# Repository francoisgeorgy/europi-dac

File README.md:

# A 4 channels DAC for the EuroPi

This is a custom PCB that add a four channels DAC to the [EuroPi](https://allensynthesis.co.uk/modules/europi.html).

The DAC is a [MCP4728](https://www.microchip.com/en-us/product/mcp4728) : 

* 12-Bit Resolution
* 4 Buffered Voltage Outputs
* Single-Supply Operation: 2.7V to 5.5V
* On-Board Non-Volatile Memory (EEPROM)
* Normal or Power-Down Mode
* Internal or External Voltage Reference Selection
* Rail-to-Rail Output
* Low Power Consumption
* ±0.2 LSB DNL (typical)
* Address bits: User Programmable toEEPROM
* Standard (100 kbps), Fast (400 kbps) and High Speed (3.4 Mbps) Modes

The voltage reference is a [LM4040](https://www.analog.com/en/products/lm4040.html), 3.0V. 

The DAC outputs are connected to the EuroPi 3, 4, 5 and 6 outputs as follows : 

| EuroPi output | DAC channel |
|--------------:|------------:|
|             1 |             |
|             2 |             |
|             3 |           D |
|             4 |           B |
|             5 |           C |
|             6 |           A |

This specific order of the channels was chosen to facilitate the PCB routing. 

The EuroPi outputs 1 and 2 do not change and are still driven with a PWM output from the Pico.

#### Power supply : 

This custom PCB swaps the 10-pin Eurorack power connector for a 16-pin one and removes the onboard power regulator, 
opting to use the 5V directly from the Eurorack power supply instead.

## Schematic

Here is the schematic of this PCB : [dac-board-v2.1.pdf](hardware%2Fdac-board-v2.1%2Fplot%2Fdac-board-v2.1.pdf)

## Why build this custom PCB?

This PCB project was mainly a fun excuse to experiment and learn:

- [KiCad](https://www.kicad.org/) practice: a good opportunity to get better at PCB design.
- SMD assembly with [JLCPCB](https://jlcpcb.com/): tried out having the board made and assembled by an external provider.
- Eurorack power filtering: played around with filtering power right on the PCB.
- DAC vs PWM outputs: wanted to see if DAC outputs really outperform PWM for basic CV voltages.
- Just for fun: because DIY projects are always more fun!

## License

This custom PCB is licensed under the same terms and conditions as the original EuroPi. 

This module, and any documentation included in this repository, is entirely "free" software and hardware, 
under different licenses depending on the software, hardware, and documentation itself.

* Software: [Apache 2.0](software/LICENSE)
* Hardware: [CERN OHL-S v2](hardware/LICENSE)
* Documentation: [CC0 1.0](LICENSE)

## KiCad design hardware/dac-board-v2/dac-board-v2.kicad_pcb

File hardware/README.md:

## PCB versions

### [dac-board](dac-board) 

Do not use this version. The J2 and J3 connectors (headers that link the front panel) are incorrectly oriented.

### [dac-board-v2](dac-board-v2) 

This version is OK and has been successfully used with a regular EuroPi front-panel. 

### [dac-board-v2.1](dac-board-v2.1) 

This minor release fixes the connectors placement in KiCad. This version has not been tested yet.

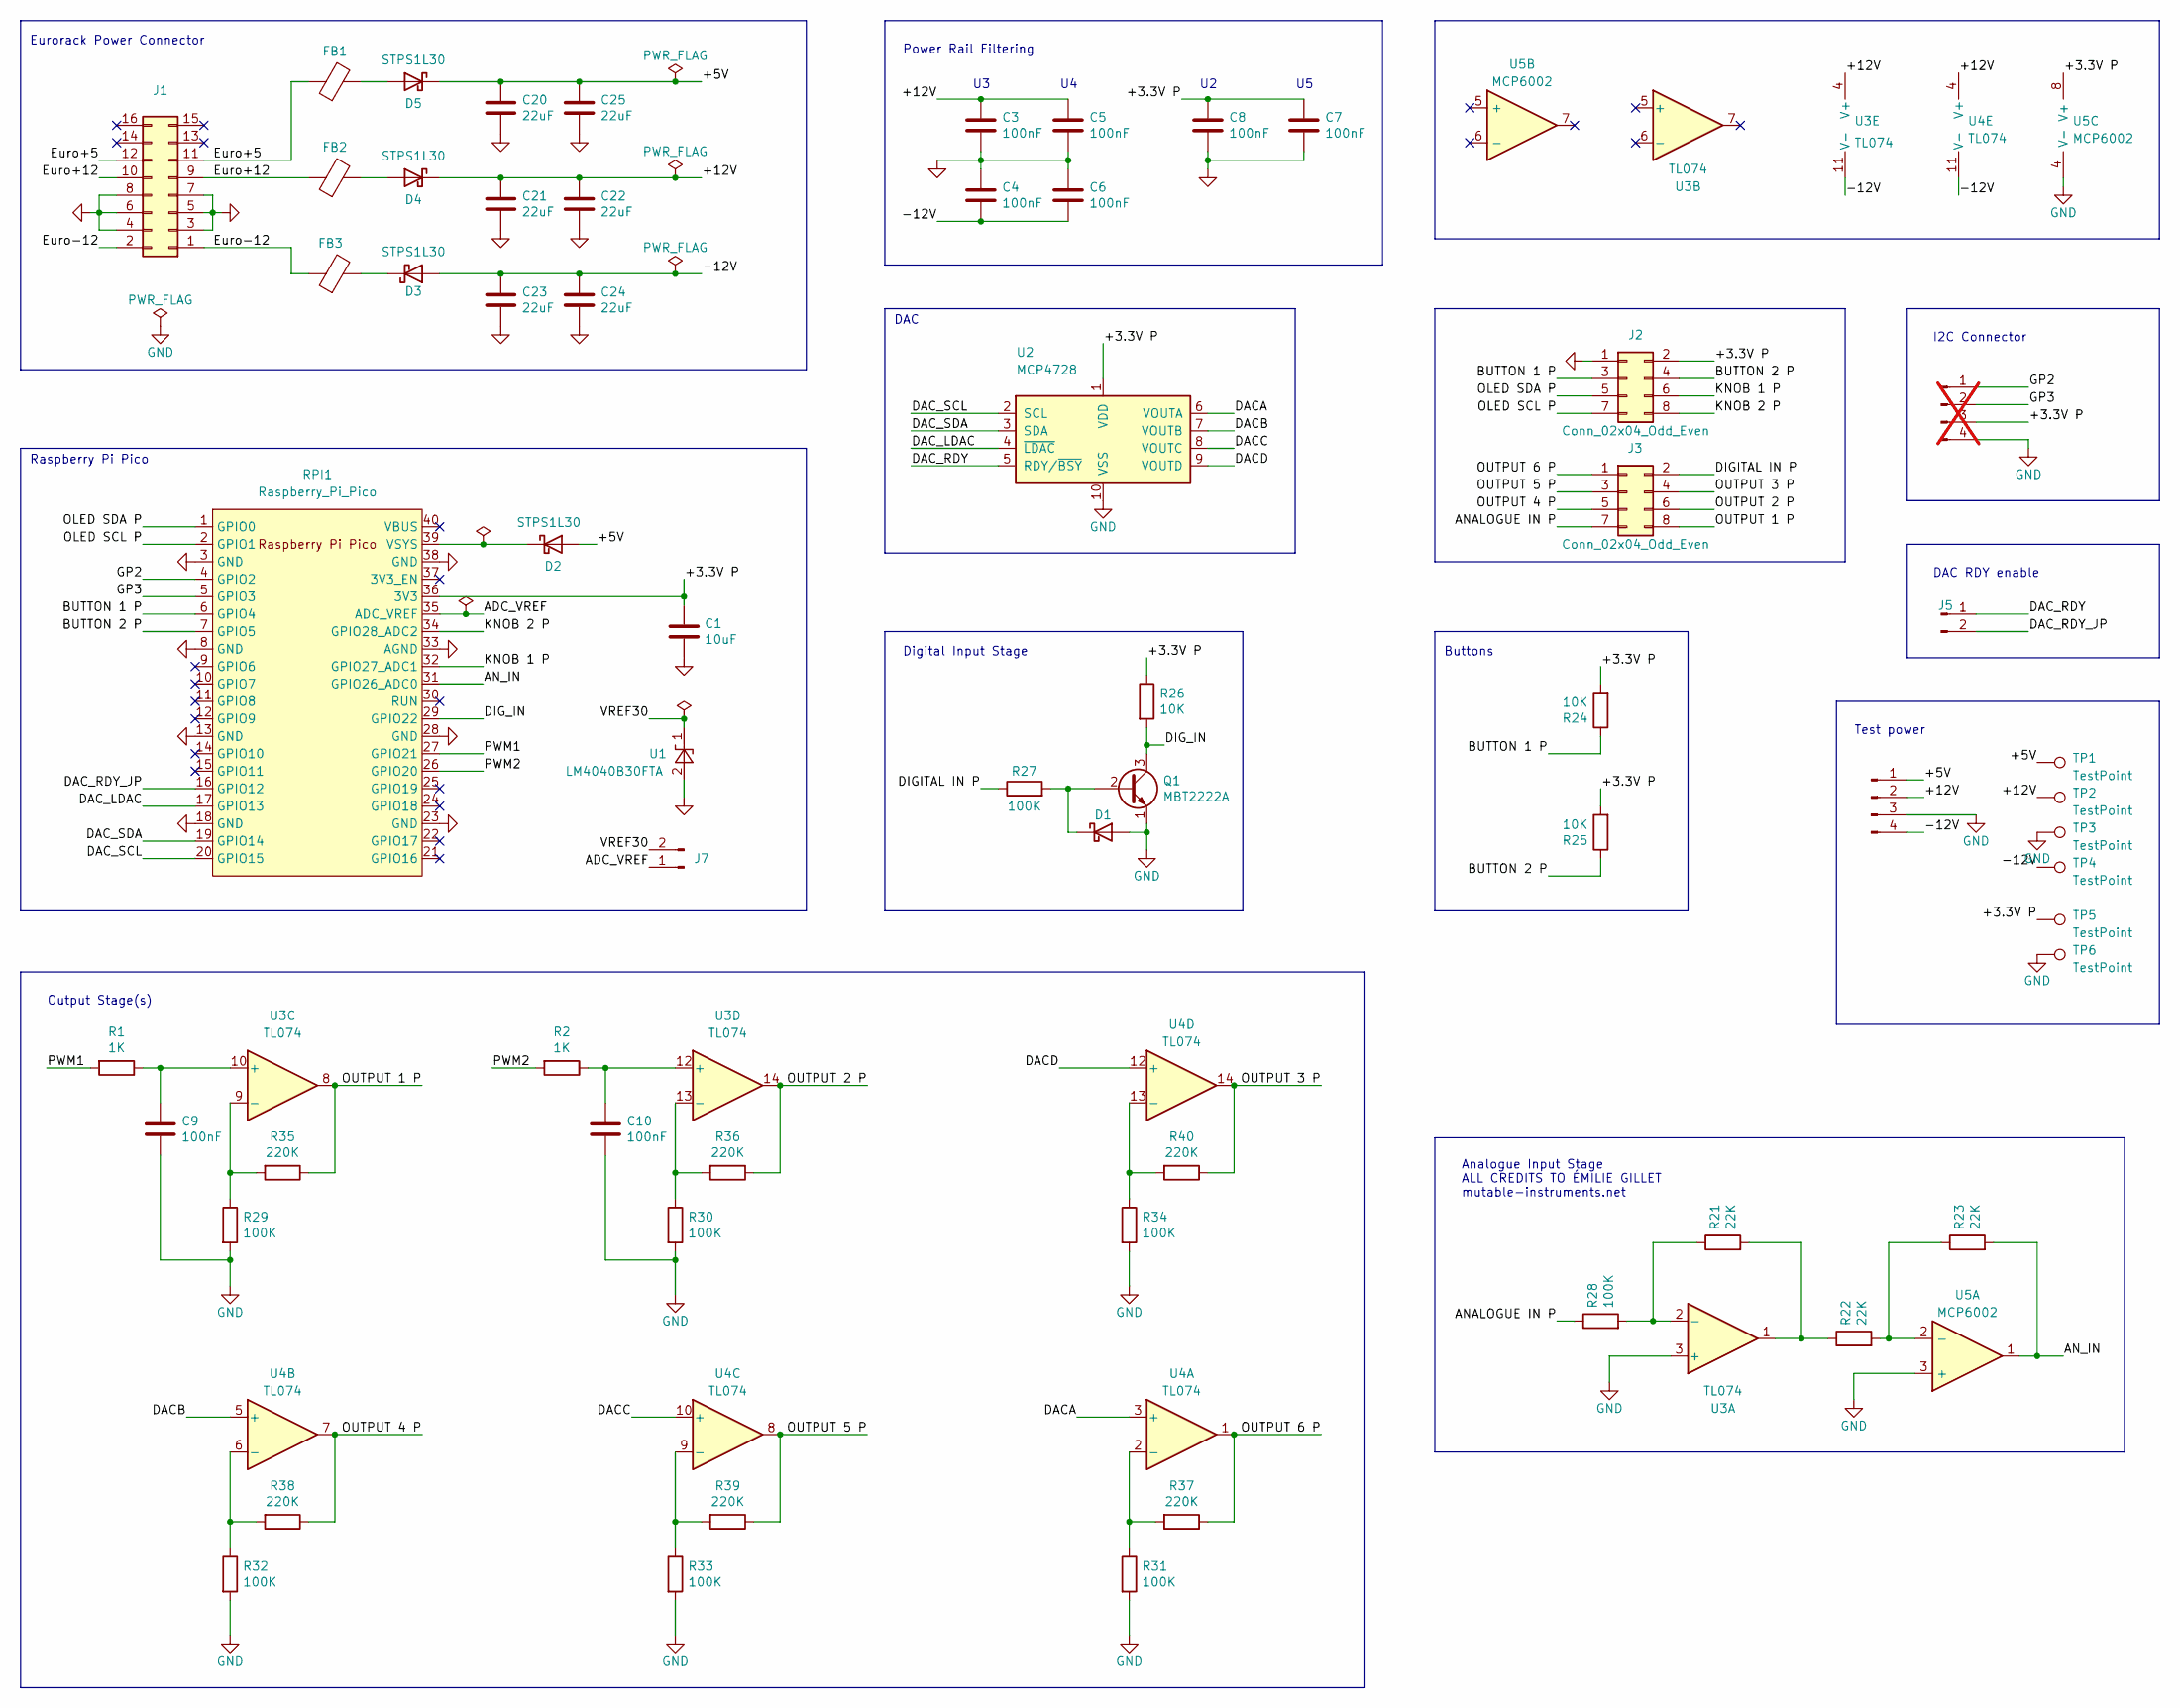
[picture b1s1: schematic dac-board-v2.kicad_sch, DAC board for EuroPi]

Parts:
C1: 10uF; C_0805_2012Metric; JLCPCB Part # C15850
C3, C4, C5, C6, C7, C8, C9, C10: 100nF; C_0402_1005Metric
C20, C21, C22, C23, C24, C25: 22uF; C_1206_3216Metric; JLCPCB Part # C12891
D1: 1N5817WS; D_SOD-323; JLCPCB Part # C727114
D2, D3, D4, D5: STPS1L30; D_SMA; JLCPCB Part # C157388
FB1, FB2, FB3: FerriteBead; L_0805_2012Metric; JLCPCB Part # C216152
J1: Conn_02x08_Odd_Even; IDC-Header_2x08_P2.54mm_Vertical
J2, J3: Conn_02x04_Odd_Even; PinSocket_2x04_P2.54mm_Vertical
J4: Conn_01x04_Male; PinHeader_1x04_P2.54mm_Vertical; not fitted
J5: Conn_01x02_Pin; PinHeader_1x02_P2.54mm_Horizontal
J6: Conn_01x04_Male; PinHeader_1x04_P2.54mm_Vertical
J7: Conn_01x02_Pin; PinHeader_1x02_P2.54mm_Vertical
Q1: MBT2222A; SOT-23; JLCPCB Part # C8512
R1, R2: 1K; R_0402_1005Metric
R21, R22, R23: 22K; R_0402_1005Metric
R24, R25, R26: 10K; R_0402_1005Metric
R27, R28, R29, R30, R31, R32, R33, R34: 100K; R_0402_1005Metric
R35, R36, R37, R38, R39, R40: 220K; R_0402_1005Metric
RPI1: Raspberry_Pi_Pico; Raspberry Pi Pico
TP1, TP2, TP3, TP4, TP5, TP6: TestPoint; TestPoint_Pad_D2.0mm
U1: LM4040B30FTA; SOT-23; JLCPCB Part # C460604
U2: MCP4728; MSOP-10_3x3mm_P0.5mm; JLCPCB Part # C108207
U3, U4: TL074; SOIC-14_3.9x8.7mm_P1.27mm; JLCPCB Part # C107644
U5: MCP6002; SOIC-8_3.9x4.9mm_P1.27mm; JLCPCB Part # C7377

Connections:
/+3.3V P: C1.1, C7.1, C8.1, J2.2, J4.3, R24.2, R25.2, R26.1, RPI1.36 (3V3), TP5.1, U2.1 (VDD), U5.8 (V+)
/+5V: C20.1, C25.1, D2.2 (A), D5.1 (K), J6.1, TP1.1
/+12V: C3.1, C5.1, C21.1, C22.1, D4.1 (K), J6.2, TP2.1, U3.4 (V+), U4.4 (V+)
/-12V: C4.2, C6.2, C23.1, C24.1, D3.2 (A), J6.4, TP4.1, U3.11 (V-), U4.11 (V-)
/ADC_VREF: J7.1, RPI1.35 (ADC_VREF)
/ANALOGUE IN P: J3.7, R28.1
/AN_IN: R23.2, RPI1.31 (GPIO26_ADC0), U5.1
/BUTTON 1 P: J2.3, R24.1, RPI1.6 (GPIO4)
/BUTTON 2 P: J2.4, R25.1, RPI1.7 (GPIO5)
/DACA: U2.6 (VOUTA), U4.3 (+)
/DACB: U2.7 (VOUTB), U4.5 (+)
/DACC: U2.8 (VOUTC), U4.10 (+)
/DACD: U2.9 (VOUTD), U4.12 (+)
/DAC_LDAC: RPI1.17 (GPIO13), U2.4 (~LDAC)
/DAC_RDY: J5.1, U2.5 (RDY/~BSY)
/DAC_RDY_JP: J5.2, RPI1.16 (GPIO12)
/DAC_SCL: RPI1.20 (GPIO15), U2.2 (SCL)
/DAC_SDA: RPI1.19 (GPIO14), U2.3 (SDA)
/DIGITAL IN P: J3.2, R27.1
/DIG_IN: Q1.3 (C), R26.2, RPI1.29 (GPIO22)
/Euro+5: FB1.1, J1.11, J1.12
/Euro+12: FB2.1, J1.9, J1.10
/Euro-12: FB3.1, J1.1, J1.2
/GP2: J4.1, RPI1.4 (GPIO2)
/GP3: J4.2, RPI1.5 (GPIO3)
/KNOB 1 P: J2.6, RPI1.32 (GPIO27_ADC1)
/KNOB 2 P: J2.8, RPI1.34 (GPIO28_ADC2)
/OLED SCL P: J2.7, RPI1.2 (GPIO1)
/OLED SDA P: J2.5, RPI1.1 (GPIO0)
/OUTPUT 1 P: J3.8, R35.1, U3.8
/OUTPUT 2 P: J3.6, R36.1, U3.14
/OUTPUT 3 P: J3.4, R40.1, U4.14
/OUTPUT 4 P: J3.5, R38.1, U4.7
/OUTPUT 5 P: J3.3, R39.1, U4.8
/OUTPUT 6 P: J3.1, R37.1, U4.1
/PWM1: R1.2, RPI1.27 (GPIO21)
/PWM2: R2.2, RPI1.26 (GPIO20)
/VREF30: J7.2, U1.1 (K)
GND: C1.2, C3.2, C4.1, C5.2, C6.1, C7.2, C8.2, C9.2, C10.2, C20.2, C21.2, C22.2, C23.2, C24.2, C25.2, D1.2 (A), J1.3, J1.4, J1.5, J1.6, J1.7, J1.8, J2.1, J4.4, J6.3, Q1.1 (E), R29.2, R30.2, R31.2, R32.2, R33.2, R34.2, RPI1.3 (GND), RPI1.8 (GND), RPI1.13 (GND), RPI1.18 (GND), RPI1.23 (GND), RPI1.28 (GND), RPI1.33 (AGND), RPI1.38 (GND), TP3.1, TP6.1, U1.2 (A), U2.10 (VSS), U3.3 (+), U5.3 (+), U5.4 (V-)
unnamed: D2.1 (K), RPI1.39 (VSYS)
unnamed: D1.1 (K), Q1.2 (B), R27.2
unnamed: D3.1 (K), FB3.2
unnamed: D4.2 (A), FB2.2
unnamed: D5.2 (A), FB1.2
unnamed: R21.2, R22.1, U3.1
unnamed: R21.1, R28.2, U3.2 (-)
unnamed: C9.1, R1.1, U3.10 (+)
unnamed: R29.1, R35.2, U3.9 (-)
unnamed: C10.1, R2.1, U3.12 (+)
unnamed: R30.1, R36.2, U3.13 (-)
unnamed: R31.1, R37.2, U4.2 (-)
unnamed: R32.1, R38.2, U4.6 (-)
unnamed: R33.1, R39.2, U4.9 (-)
unnamed: R34.1, R40.2, U4.13 (-)
unnamed: R22.2, R23.1, U5.2 (-)

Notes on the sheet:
Buttons
Analogue Input Stage ALL CREDITS TO ÉMILIE GILLET mutable-instruments.net
Power Rail Filtering
Eurorack Power Connector
I2C Connector
Digital Input Stage
DAC
Raspberry Pi Pico
Output Stage(s)
Test power
DAC RDY enable

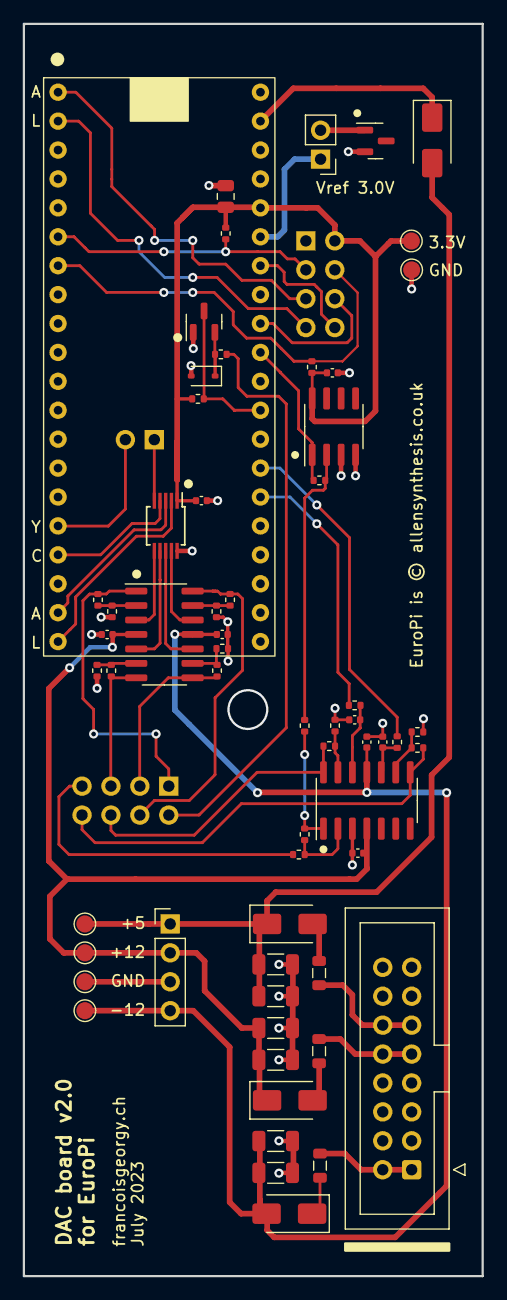
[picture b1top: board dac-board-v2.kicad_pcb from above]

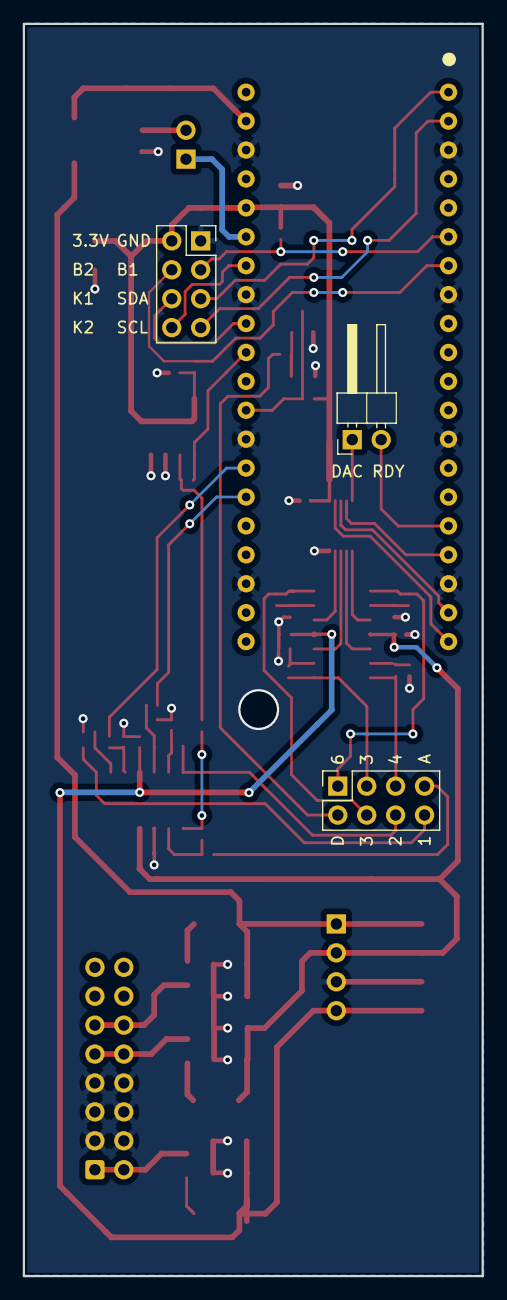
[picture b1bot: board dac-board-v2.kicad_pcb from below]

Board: 2 copper layers, 40.3 x 110.0 mm, 64 parts (3 on the bottom side), 53 nets.

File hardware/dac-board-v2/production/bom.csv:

Designator,Footprint,Quantity,Value,LCSC Part #
C1,0805,1,10uF,C15850
"C10, C3, C4, C5, C6, C7, C8, C9",0402,8,100nF,
"C20, C21, C22, C23, C24, C25",1206,6,22uF,C12891
D1,D_SOD-323,1,1N5817WS,C727114
"D2, D3, D4, D5",D_SMA,4,STPS1L30,C157388
"FB1, FB2, FB3",0805,3,FerriteBead,C216152
"J2, J3",PinSocket_2x04_P2.54mm_Vertical,2,Conn_02x04_Odd_Even,
Q1,SOT-23,1,MBT2222A,C8512
"R1, R2",0402,2,1K,
"R21, R22, R23",0402,3,22K,
"R24, R25, R26",0402,3,10K,
"R27, R28, R29, R30, R31, R32, R33, R34",0402,8,100K,
"R35, R36, R37, R38, R39, R40",0402,6,220K,
"TP1, TP2, TP3, TP4, TP5, TP6",TestPoint_Pad_D1.5mm,6,TestPoint,
U1,SOT-23,1,LM4040B30FTA,C460604
U2,MSOP-10_3x3mm_P0.5mm,1,MCP4728,C108207
"U3, U4",SOIC-14_3.9x8.7mm_P1.27mm,2,TL074,C107644
U5,SOIC-8_3.9x4.9mm_P1.27mm,1,MCP6002,C7377

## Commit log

2024-09-17 Cleaning
2024-09-17 Licenses
2024-09-17 Documentation

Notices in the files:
hardware/dac-board-v2/dac-board-v2.kicad_pcb:
EuroPi is © allensynthesis.co.uk
hardware/dac-board-v2/dac-board-v2.kicad_sch:
CC BY-SA 3.0
